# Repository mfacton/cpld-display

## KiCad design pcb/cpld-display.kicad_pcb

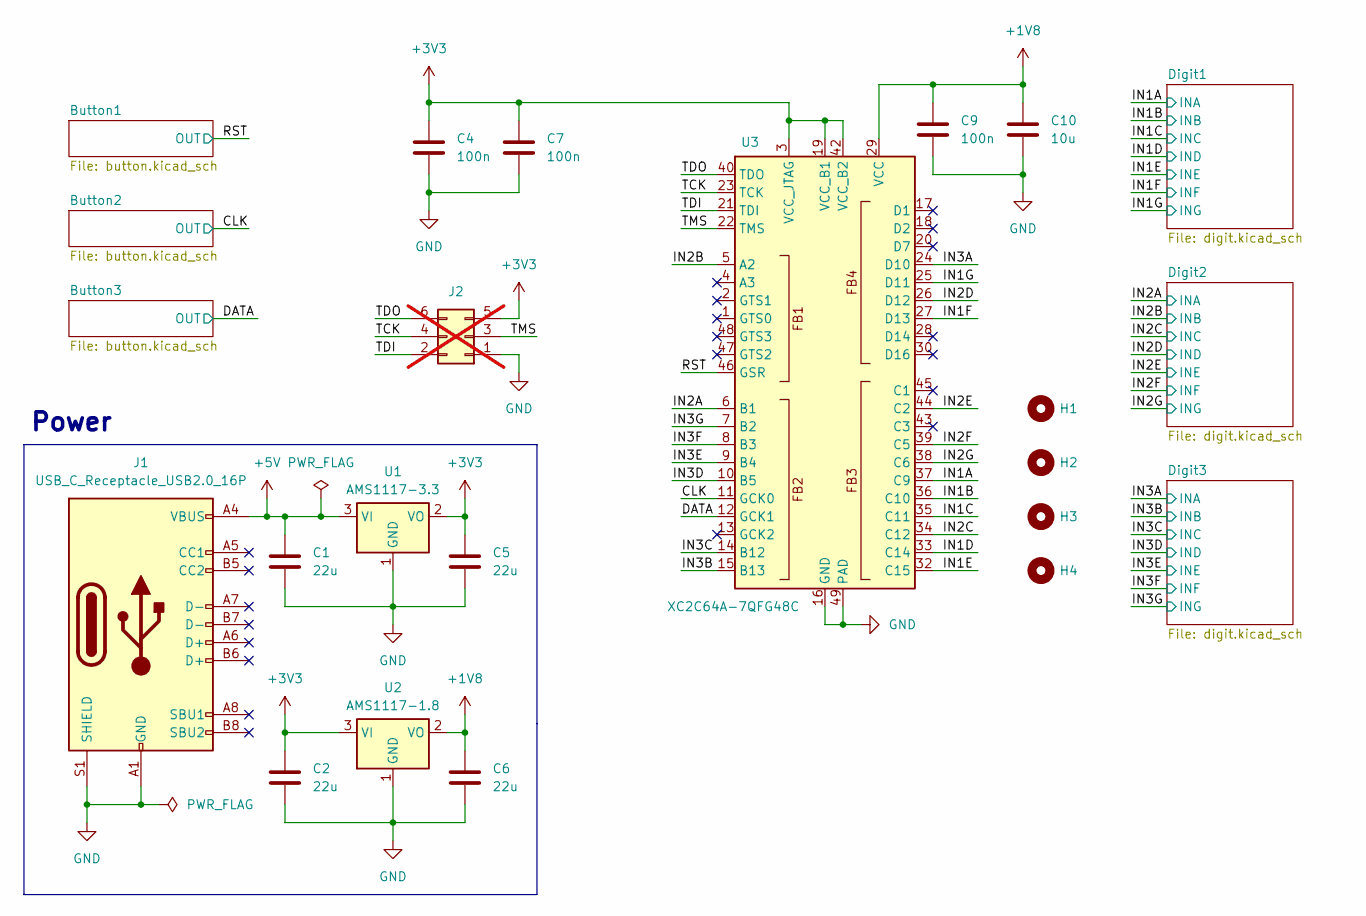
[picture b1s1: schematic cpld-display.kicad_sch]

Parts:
C1: 22u; C_0805_2012Metric; LCSC C45783
C2, C5, C6: 22u; C_0603_1608Metric; LCSC C59461
C4, C7, C9: 100n; C_0402_1005Metric; LCSC C1525
C10: 10u; C_0402_1005Metric; LCSC C15525
H1, H2, H3, H4: MountingHole; MountingHole_3.2mm_M3
J1: USB_C_Receptacle_USB2.0_16P; USB_C_Receptacle_GCT_USB4105-xx-A_16P_TopMnt_Horizontal; LCSC C165948
J2: Conn_02x03_Odd_Even; PinHeader_2x03_P2.54mm_Vertical; not fitted
U1: AMS1117-3.3; SOT-223-3_TabPin2; LCSC C6186
U2: AMS1117-1.8; SOT-223-3_TabPin2; LCSC C347220
U3: XC2C64A-7QFG48C; QFN-48-1EP_7x7mm_P0.5mm_EP5.15x5.15mm; LCSC C1519023

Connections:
+1V8: C6.1, C9.1, C10.1, U2.2 (VO), U3.29 (VCC)
+3V3: C2.1, C4.1, C5.1, C7.1, J2.5, U1.2 (VO), U2.3 (VI), U3.3 (VCC_JTAG), U3.19 (VCC_B1), U3.42 (VCC_B2); also elsewhere on the board
+5V: C1.1, J1.A4 (VBUS), J1.A9 (VBUS), J1.B4 (VBUS), J1.B9 (VBUS), U1.3 (VI)
/CLK: U3.11 (GCK0); also elsewhere on the board
/DATA: U3.12 (GCK1); also elsewhere on the board
/IN1A: U3.37 (C9); also elsewhere on the board
/IN1B: U3.36 (C10); also elsewhere on the board
/IN1C: U3.35 (C11); also elsewhere on the board
/IN1D: U3.33 (C14); also elsewhere on the board
/IN1E: U3.32 (C15); also elsewhere on the board
/IN1F: U3.27 (D13); also elsewhere on the board
/IN1G: U3.25 (D11); also elsewhere on the board
/IN2A: U3.6 (B1); also elsewhere on the board
/IN2B: U3.5 (A2); also elsewhere on the board
/IN2C: U3.34 (C12); also elsewhere on the board
/IN2D: U3.26 (D12); also elsewhere on the board
/IN2E: U3.44 (C2); also elsewhere on the board
/IN2F: U3.39 (C5); also elsewhere on the board
/IN2G: U3.38 (C6); also elsewhere on the board
/IN3A: U3.24 (D10); also elsewhere on the board
/IN3B: U3.15 (B13); also elsewhere on the board
/IN3C: U3.14 (B12); also elsewhere on the board
/IN3D: U3.10 (B5); also elsewhere on the board
/IN3E: U3.9 (B4); also elsewhere on the board
/IN3F: U3.8 (B3); also elsewhere on the board
/IN3G: U3.7 (B2); also elsewhere on the board
/RST: U3.46 (GSR); also elsewhere on the board
/TCK: J2.4, U3.23 (TCK)
/TDI: J2.2, U3.21 (TDI)
/TDO: J2.6, U3.40 (TDO)
/TMS: J2.3, U3.22 (TMS)
GND: C1.2, C2.2, C4.2, C5.2, C6.2, C7.2, C9.2, C10.2, J1.A1 (GND), J1.A12 (GND), J1.B1 (GND), J1.B12 (GND), J1.S1 (SHIELD), J2.1, U1.1 (GND), U2.1 (GND), U3.16 (GND), U3.31 (GND), U3.41 (GND), U3.49 (PAD); also elsewhere on the board

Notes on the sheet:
Power

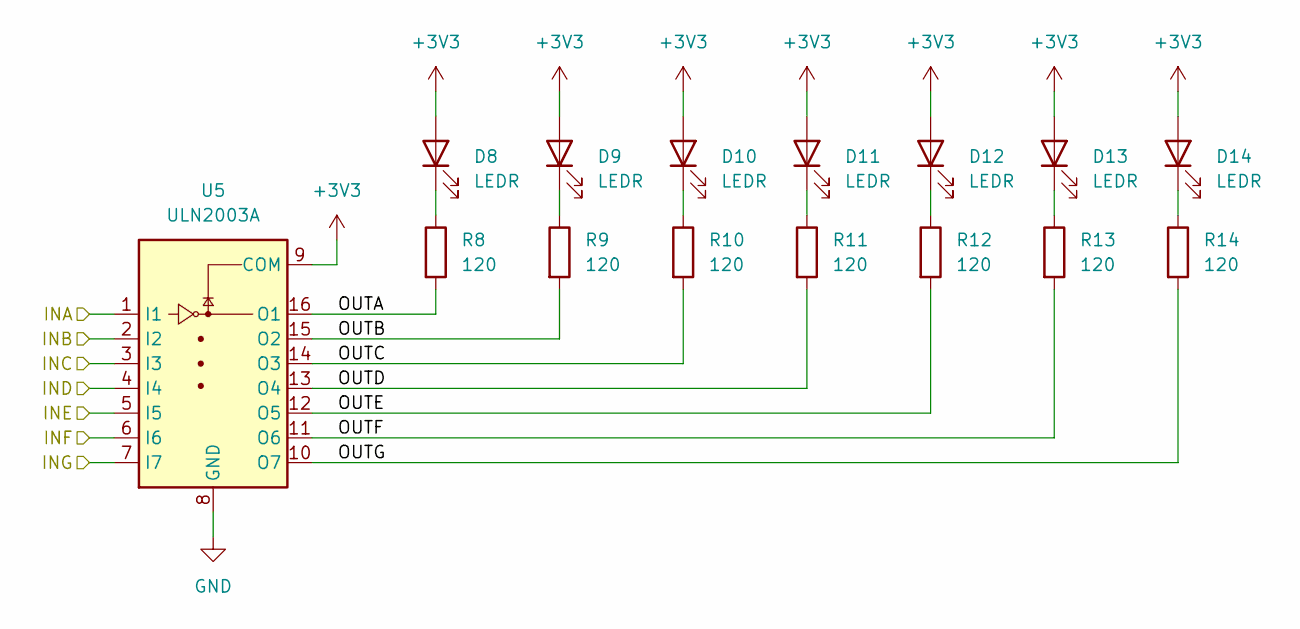
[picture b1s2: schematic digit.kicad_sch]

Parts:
D8, D9, D10, D11, D12, D13, D14: LEDR; LED_0603_1608Metric; LCSC C2286
R8, R9, R10, R11, R12, R13, R14: 120; R_0603_1608Metric; LCSC C22787
U5: ULN2003A; SOIC-16_3.9x9.9mm_P1.27mm; LCSC C7512

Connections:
+3V3: D8.2 (A), D9.2 (A), D10.2 (A), D11.2 (A), D12.2 (A), D13.2 (A), D14.2 (A), U5.9 (COM); also elsewhere on the board
/Digit2/OUTA: R8.2, U5.16 (O1)
/Digit2/OUTB: R9.2, U5.15 (O2)
/Digit2/OUTC: R10.2, U5.14 (O3)
/Digit2/OUTD: R11.2, U5.13 (O4)
/Digit2/OUTE: R12.2, U5.12 (O5)
/Digit2/OUTF: R13.2, U5.11 (O6)
/Digit2/OUTG: R14.2, U5.10 (O7)
/IN2A: U5.1 (I1); also elsewhere on the board
/IN2B: U5.2 (I2); also elsewhere on the board
/IN2C: U5.3 (I3); also elsewhere on the board
/IN2D: U5.4 (I4); also elsewhere on the board
/IN2E: U5.5 (I5); also elsewhere on the board
/IN2F: U5.6 (I6); also elsewhere on the board
/IN2G: U5.7 (I7); also elsewhere on the board
GND: U5.8 (GND); also elsewhere on the board
unnamed: D8.1 (K), R8.1
unnamed: D9.1 (K), R9.1
unnamed: D10.1 (K), R10.1
unnamed: D11.1 (K), R11.1
unnamed: D12.1 (K), R12.1
unnamed: D13.1 (K), R13.1
unnamed: D14.1 (K), R14.1

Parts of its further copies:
D1, D2, D3, D4, D5, D6, D7, D15, D16, D17, D18, D19, D20, D21: LEDR; LED_0603_1608Metric; LCSC C2286
R1, R2, R3, R4, R5, R6, R7, R15, R16, R17, R18, R19, R20, R21: 120; R_0603_1608Metric; LCSC C22787
U4, U6: ULN2003A; SOIC-16_3.9x9.9mm_P1.27mm; LCSC C7512

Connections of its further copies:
+3V3: D1.2 (A), D2.2 (A), D3.2 (A), D4.2 (A), D5.2 (A), D6.2 (A), D7.2 (A), D15.2 (A), D16.2 (A), D17.2 (A), D18.2 (A), D19.2 (A), D20.2 (A), D21.2 (A), U4.9 (COM), U6.9 (COM); also elsewhere on the board
/Digit1/OUTA: R1.2, U4.16 (O1)
/Digit1/OUTB: R2.2, U4.15 (O2)
/Digit1/OUTC: R3.2, U4.14 (O3)
/Digit1/OUTD: R4.2, U4.13 (O4)
/Digit1/OUTE: R5.2, U4.12 (O5)
/Digit1/OUTF: R6.2, U4.11 (O6)
/Digit1/OUTG: R7.2, U4.10 (O7)
/Digit3/OUTA: R15.2, U6.16 (O1)
/Digit3/OUTB: R16.2, U6.15 (O2)
/Digit3/OUTC: R17.2, U6.14 (O3)
/Digit3/OUTD: R18.2, U6.13 (O4)
/Digit3/OUTE: R19.2, U6.12 (O5)
/Digit3/OUTF: R20.2, U6.11 (O6)
/Digit3/OUTG: R21.2, U6.10 (O7)
/IN1A: U4.1 (I1); also elsewhere on the board
/IN1B: U4.2 (I2); also elsewhere on the board
/IN1C: U4.3 (I3); also elsewhere on the board
/IN1D: U4.4 (I4); also elsewhere on the board
/IN1E: U4.5 (I5); also elsewhere on the board
/IN1F: U4.6 (I6); also elsewhere on the board
/IN1G: U4.7 (I7); also elsewhere on the board
/IN3A: U6.1 (I1); also elsewhere on the board
/IN3B: U6.2 (I2); also elsewhere on the board
/IN3C: U6.3 (I3); also elsewhere on the board
/IN3D: U6.4 (I4); also elsewhere on the board
/IN3E: U6.5 (I5); also elsewhere on the board
/IN3F: U6.6 (I6); also elsewhere on the board
/IN3G: U6.7 (I7); also elsewhere on the board
GND: U4.8 (GND), U6.8 (GND); also elsewhere on the board
unnamed: D1.1 (K), R1.1
unnamed: D2.1 (K), R2.1
unnamed: D3.1 (K), R3.1
unnamed: D4.1 (K), R4.1
unnamed: D5.1 (K), R5.1
unnamed: D6.1 (K), R6.1
unnamed: D7.1 (K), R7.1
unnamed: D15.1 (K), R15.1
unnamed: D16.1 (K), R16.1
unnamed: D17.1 (K), R17.1
unnamed: D18.1 (K), R18.1
unnamed: D19.1 (K), R19.1
unnamed: D20.1 (K), R20.1
unnamed: D21.1 (K), R21.1

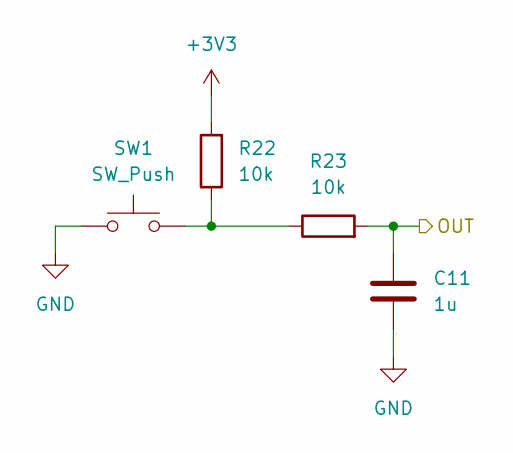
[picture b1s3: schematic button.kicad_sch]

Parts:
C11: 1u; C_0402_1005Metric; LCSC C52923
R22, R23: 10k; R_0402_1005Metric; LCSC C25744
SW1: SW_Push; SW_SPST_TL3342; LCSC C318884

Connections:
+3V3: R22.2; also elsewhere on the board
/RST: C11.1, R23.2; also elsewhere on the board
GND: C11.2, SW1.1; also elsewhere on the board
unnamed: R22.1, R23.1, SW1.2

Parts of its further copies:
C12, C13: 1u; C_0402_1005Metric; LCSC C52923
R24, R25, R26, R27: 10k; R_0402_1005Metric; LCSC C25744
SW2, SW3: SW_Push; SW_SPST_TL3342; LCSC C318884

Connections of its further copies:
+3V3: R24.2, R26.2; also elsewhere on the board
/CLK: C12.1, R25.2; also elsewhere on the board
/DATA: C13.1, R27.2; also elsewhere on the board
GND: C12.2, C13.2, SW2.1, SW3.1; also elsewhere on the board
unnamed: R24.1, R25.1, SW2.2
unnamed: R26.1, R27.1, SW3.2

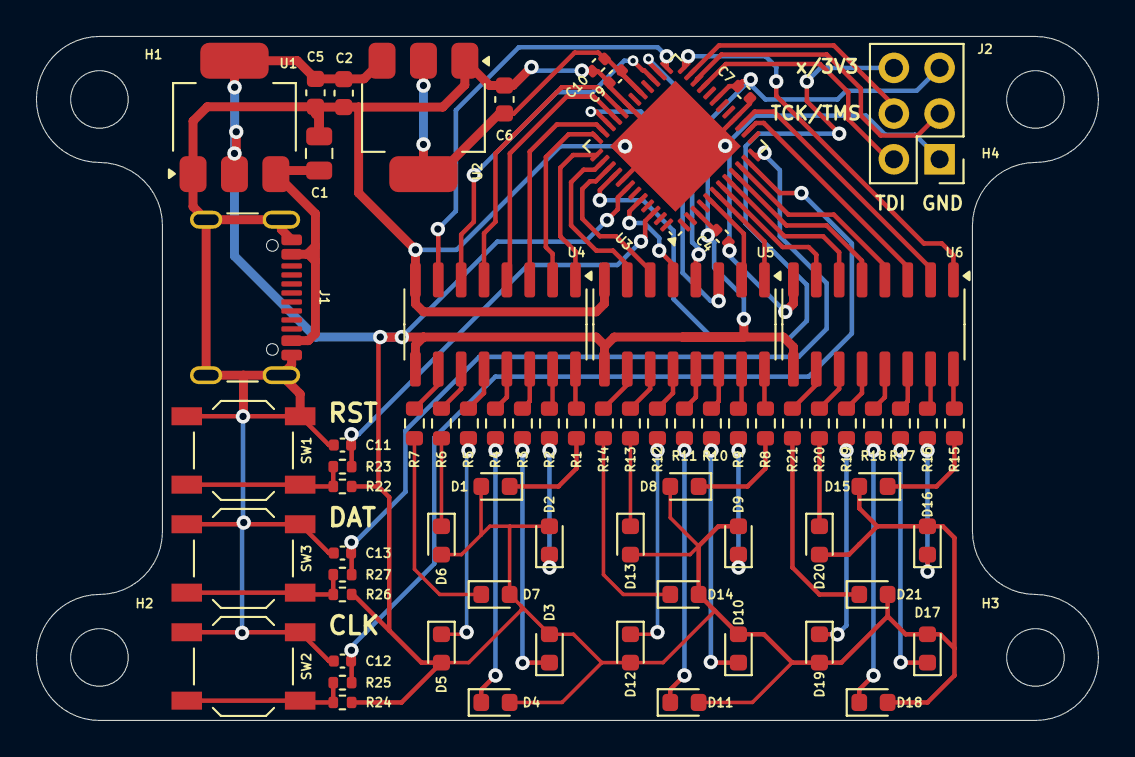
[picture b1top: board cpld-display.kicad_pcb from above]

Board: 2 copper layers, 59.0 x 38.0 mm, 74 parts (0 on the bottom side), 77 nets.

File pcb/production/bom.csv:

Designator,Footprint,Quantity,Value,LCSC Part #
C1,0805,1,22u,C45783
C10,0402,1,10u,C15525
"C11, C12, C13",0402,3,1u,C52923
"C2, C5, C6",0603,3,22u,C59461
"C4, C7, C9",0402,3,100n,C1525
"D1, D10, D11, D12, D13, D14, D15, D16, D17, D18, D19, D2, D20, D21, D3, D4, D5, D6, D7, D8, D9",0603,21,LEDR,C2286
J1,USB_C_Receptacle_GCT_USB4105-xx-A_16P_TopMnt_Horizontal,1,USB_C_Receptacle_USB2.0_16P,C165948
"R1, R10, R11, R12, R13, R14, R15, R16, R17, R18, R19, R2, R20, R21, R3, R4, R5, R6, R7, R8, R9",0603,21,120,C22787
"R22, R23, R24, R25, R26, R27",0402,6,10k,C25744
"SW1, SW2, SW3",SW_SPST_TL3342,3,SW_Push,C318884
U1,SOT-223-3_TabPin2,1,AMS1117-3.3,C6186
U2,SOT-223-3_TabPin2,1,AMS1117-1.8,C347220
U3,QFN-48-1EP_7x7mm_P0.5mm_EP5.15x5.15mm,1,XC2C64A-7QFG48C,C1519023
"U4, U5, U6",SOIC-16_3.9x9.9mm_P1.27mm,3,ULN2003A,C7512

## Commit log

2024-09-05 Add notes from fpga dev repo
2024-09-05 Finish pcb and confim verilog configuration and code
2024-09-09 Final design
2024-09-09 Change jtag production properties
2024-09-30 Fix jtag tdo pin
2024-09-30 Finish programming
2024-09-30 Add notes and ftdi config
2024-10-02 Save project
